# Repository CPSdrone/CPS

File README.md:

# CPS [Custom Printed Submarine]  

Is a project started by Filip Buława, Piotr Domanowski and Marcin Hnat. 
It is about creating a functional product of a innovative submarine, primarily with live streaming from camera in the drone. 
Project is based on 3D printing process, which allows developing various solutions for the form of a drone.

To learn more, find us on
* [Instagram](https://instagram.com/cpsdrone)
* [Facebook](https://facebook.com/cpsdrone)
* [YouTube](https://www.youtube.com/channel/UCqbdxbvG6cqnh_S_RcGnWWg)

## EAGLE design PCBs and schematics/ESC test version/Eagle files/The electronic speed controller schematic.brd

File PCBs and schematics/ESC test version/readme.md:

# ESC test version
This is a work in progress version of our own electronic speed controller for controlling **BLDC** motors featuring **I2C** communication, current and temperature sensors. This is version used only for creating the program and not the final **ESC**!

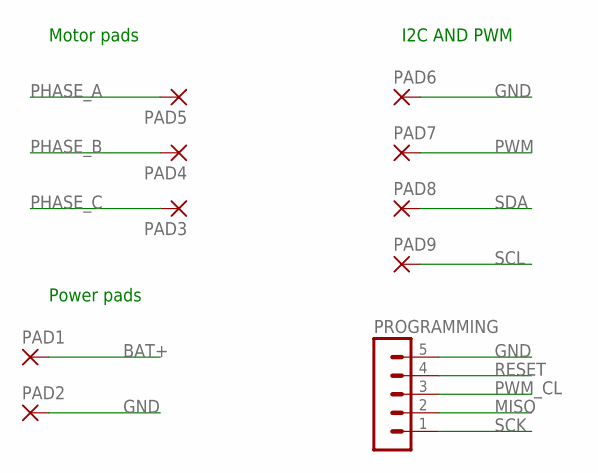
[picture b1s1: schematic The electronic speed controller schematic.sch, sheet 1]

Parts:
PAD1, PAD2, PAD3, PAD4, PAD5: SMD5; SMD2,54-5,08
PAD6, PAD7, PAD8, PAD9: SMD2; SMD1,27-2,54
PROGRAMMING: MA05-1

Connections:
BAT+: PAD1.1; also elsewhere on the board
GND: PAD2.1, PAD6.1, PROGRAMMING.5; also elsewhere on the board
MISO: PROGRAMMING.2; also elsewhere on the board
PHASE_A: PAD5.1; also elsewhere on the board
PHASE_B: PAD4.1; also elsewhere on the board
PHASE_C: PAD3.1; also elsewhere on the board
PWM: PAD7.1; also elsewhere on the board
PWM_CL: PROGRAMMING.3; also elsewhere on the board
RESET: PROGRAMMING.4; also elsewhere on the board
SCK: PROGRAMMING.1; also elsewhere on the board
SCL: PAD9.1; also elsewhere on the board
SDA: PAD8.1; also elsewhere on the board

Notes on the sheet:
Power pads
Motor pads
I2C AND PWM

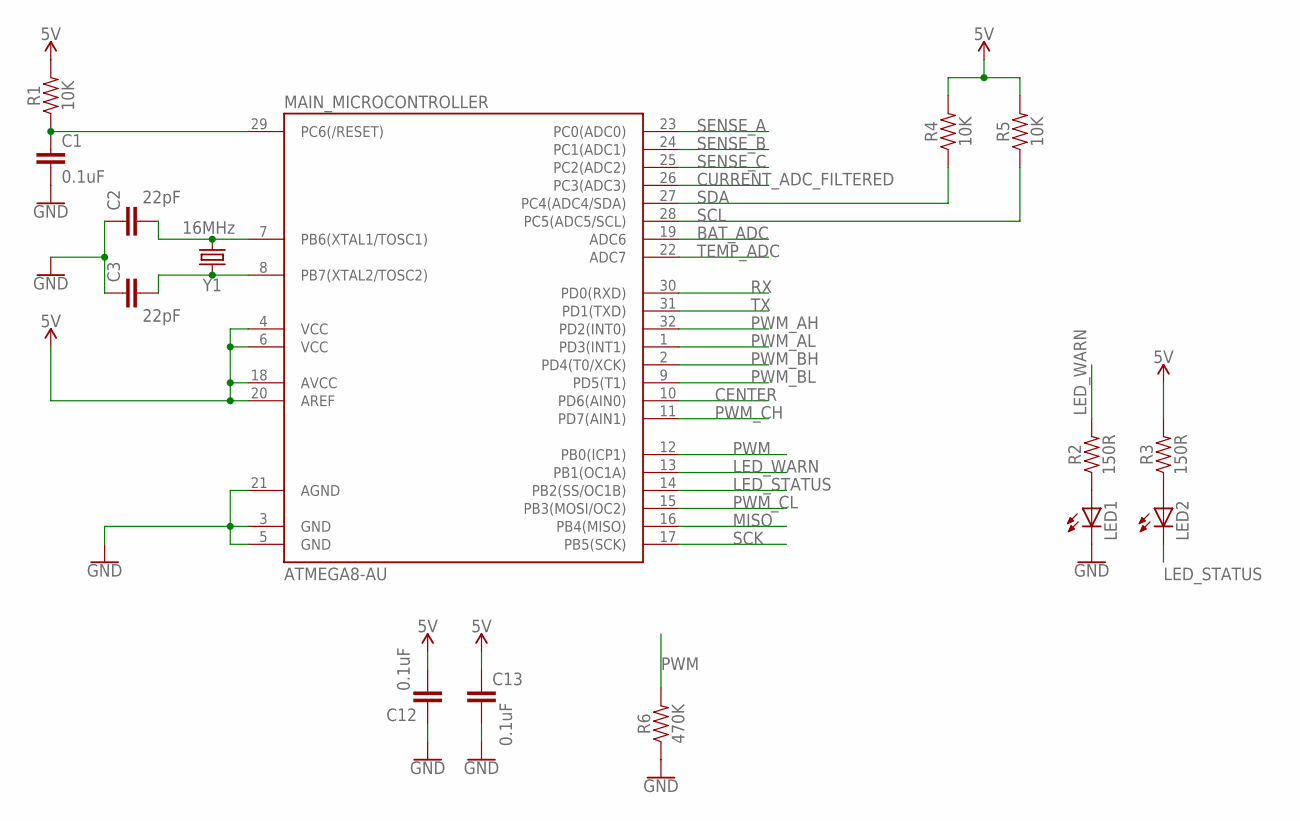
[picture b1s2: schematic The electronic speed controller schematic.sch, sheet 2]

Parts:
C1, C12, C13: 0.1uF; 0805
C2, C3: 22pF; 0805
LED1, LED2: LEDCHIPLED_0805; CHIPLED_0805
MAIN_MICROCONTROLLER: ATMEGA8-AU; TQFP32-08
R1, R4, R5: 10K; 0805
R2, R3: 150R; 0805
R6: 470K; 0805
Y1: 16MHz; CRYSTAL-SMD-5X3.2-4PAD

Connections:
5V: C12.2, C13.1, MAIN_MICROCONTROLLER.4 (VCC), MAIN_MICROCONTROLLER.6 (VCC), MAIN_MICROCONTROLLER.18 (AVCC), MAIN_MICROCONTROLLER.20 (AREF), R1.2, R3.2, R4.2, R5.2; also elsewhere on the board
BAT_ADC: MAIN_MICROCONTROLLER.19 (ADC6); also elsewhere on the board
CENTER: MAIN_MICROCONTROLLER.10 (PD6(AIN0)); also elsewhere on the board
CURRENT_ADC_FILTERED: MAIN_MICROCONTROLLER.26 (PC3(ADC3)); also elsewhere on the board
GND: C1.2, C2.1, C3.1, C12.1, C13.2, LED1.C, MAIN_MICROCONTROLLER.3 (GND), MAIN_MICROCONTROLLER.5 (GND), MAIN_MICROCONTROLLER.21 (AGND), R6.1; also elsewhere on the board
LED_STATUS: LED2.C, MAIN_MICROCONTROLLER.14 (PB2(SS/OC1B))
LED_WARN: MAIN_MICROCONTROLLER.13 (PB1(OC1A)), R2.2
MISO: MAIN_MICROCONTROLLER.16 (PB4(MISO)); also elsewhere on the board
unnamed: C2.2, MAIN_MICROCONTROLLER.7 (PB6(XTAL1/TOSC1)), Y1.3 (2)
unnamed: C3.2, MAIN_MICROCONTROLLER.8 (PB7(XTAL2/TOSC2)), Y1.1
unnamed: LED1.A, R2.1
unnamed: LED2.A, R3.1
PWM: MAIN_MICROCONTROLLER.12 (PB0(ICP1)), R6.2; also elsewhere on the board
PWM_AH: MAIN_MICROCONTROLLER.32 (PD2(INT0)); also elsewhere on the board
PWM_AL: MAIN_MICROCONTROLLER.1 (PD3(INT1)); also elsewhere on the board
PWM_BH: MAIN_MICROCONTROLLER.2 (PD4(T0/XCK)); also elsewhere on the board
PWM_BL: MAIN_MICROCONTROLLER.9 (PD5(T1)); also elsewhere on the board
PWM_CH: MAIN_MICROCONTROLLER.11 (PD7(AIN1)); also elsewhere on the board
PWM_CL: MAIN_MICROCONTROLLER.15 (PB3(MOSI/OC2)); also elsewhere on the board
RESET: C1.1, MAIN_MICROCONTROLLER.29 (PC6(/RESET)), R1.1; also elsewhere on the board
RX: MAIN_MICROCONTROLLER.30 (PD0(RXD))
SCK: MAIN_MICROCONTROLLER.17 (PB5(SCK)); also elsewhere on the board
SCL: MAIN_MICROCONTROLLER.28 (PC5(ADC5/SCL)), R5.1; also elsewhere on the board
SDA: MAIN_MICROCONTROLLER.27 (PC4(ADC4/SDA)), R4.1; also elsewhere on the board
SENSE_A: MAIN_MICROCONTROLLER.23 (PC0(ADC0)); also elsewhere on the board
SENSE_B: MAIN_MICROCONTROLLER.24 (PC1(ADC1)); also elsewhere on the board
SENSE_C: MAIN_MICROCONTROLLER.25 (PC2(ADC2)); also elsewhere on the board
TEMP_ADC: MAIN_MICROCONTROLLER.22 (ADC7); also elsewhere on the board
TX: MAIN_MICROCONTROLLER.31 (PD1(TXD))

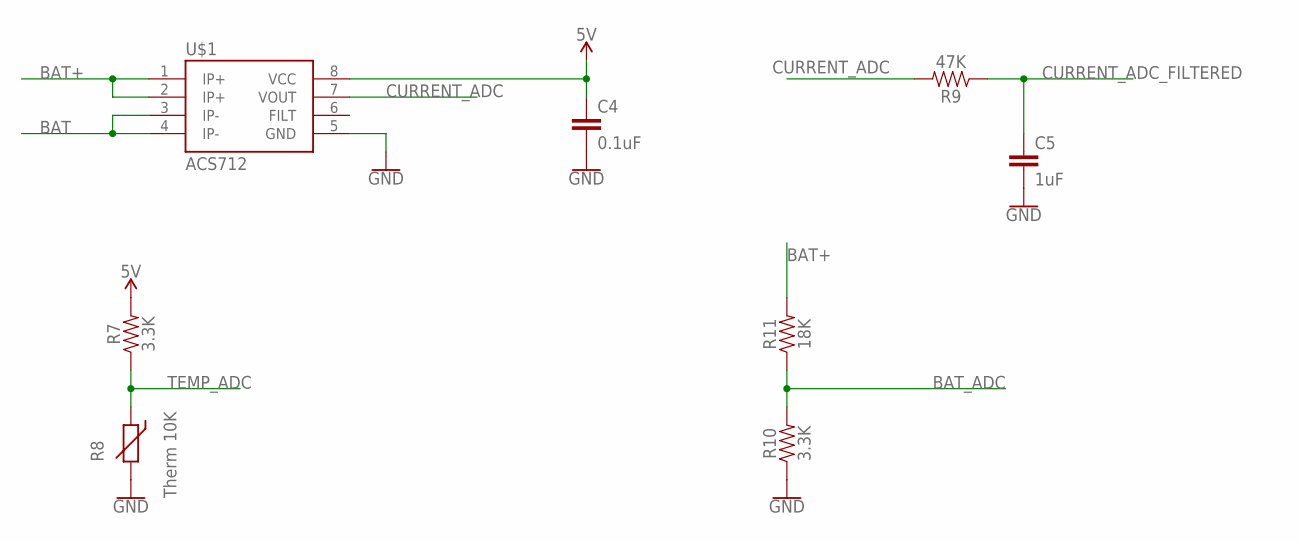
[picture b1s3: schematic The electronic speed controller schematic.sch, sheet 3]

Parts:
C4: 0.1uF; 0805
C5: 1uF; 1206
R7, R10: 3.3K; 0805
R8: Therm 10K; R-5
R9: 47K; 0805
R11: 18K; 0805
U$1: ACS712; SO08

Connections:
5V: C4.1, R7.2, U$1.8 (VCC); also elsewhere on the board
BAT: U$1.3 (IP-), U$1.4 (IP-); also elsewhere on the board
BAT+: R11.2, U$1.1 (IP+), U$1.2 (IP+); also elsewhere on the board
BAT_ADC: R10.2, R11.1; also elsewhere on the board
CURRENT_ADC: R9.2, U$1.7 (VOUT)
CURRENT_ADC_FILTERED: C5.1, R9.1; also elsewhere on the board
GND: C4.2, C5.2, R8.2, R10.1, U$1.5 (GND); also elsewhere on the board
TEMP_ADC: R7.1, R8.1; also elsewhere on the board

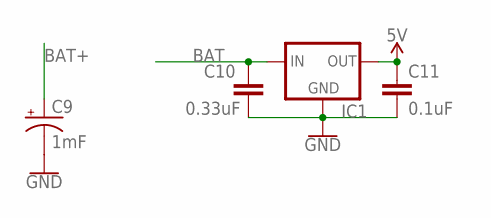
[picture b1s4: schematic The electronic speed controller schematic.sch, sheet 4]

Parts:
C9: 1mF; CPOL-RADIAL-5MM-10MM
C10: 0.33uF; 0805
C11: 0.1uF; 0805
IC1: 78LXX-SOT89; SOT89

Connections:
5V: C11.1, IC1.1 (OUT); also elsewhere on the board
BAT: C10.1, IC1.3 (IN); also elsewhere on the board
BAT+: C9.+; also elsewhere on the board
GND: C9.-, C10.2, C11.2, IC1.2 (GND); also elsewhere on the board

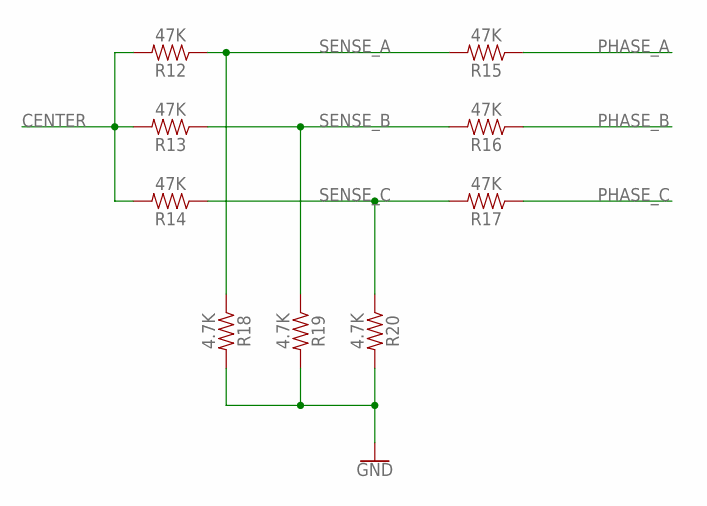
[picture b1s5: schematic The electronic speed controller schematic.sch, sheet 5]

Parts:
R12, R13, R14, R15, R16, R17: 47K; 0805
R18, R19, R20: 4.7K; 0805

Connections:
CENTER: R12.2, R13.2, R14.2; also elsewhere on the board
GND: R18.2, R19.2, R20.2; also elsewhere on the board
PHASE_A: R15.1; also elsewhere on the board
PHASE_B: R16.1; also elsewhere on the board
PHASE_C: R17.1; also elsewhere on the board
SENSE_A: R12.1, R15.2, R18.1; also elsewhere on the board
SENSE_B: R13.1, R16.2, R19.1; also elsewhere on the board
SENSE_C: R14.1, R17.2, R20.1; also elsewhere on the board

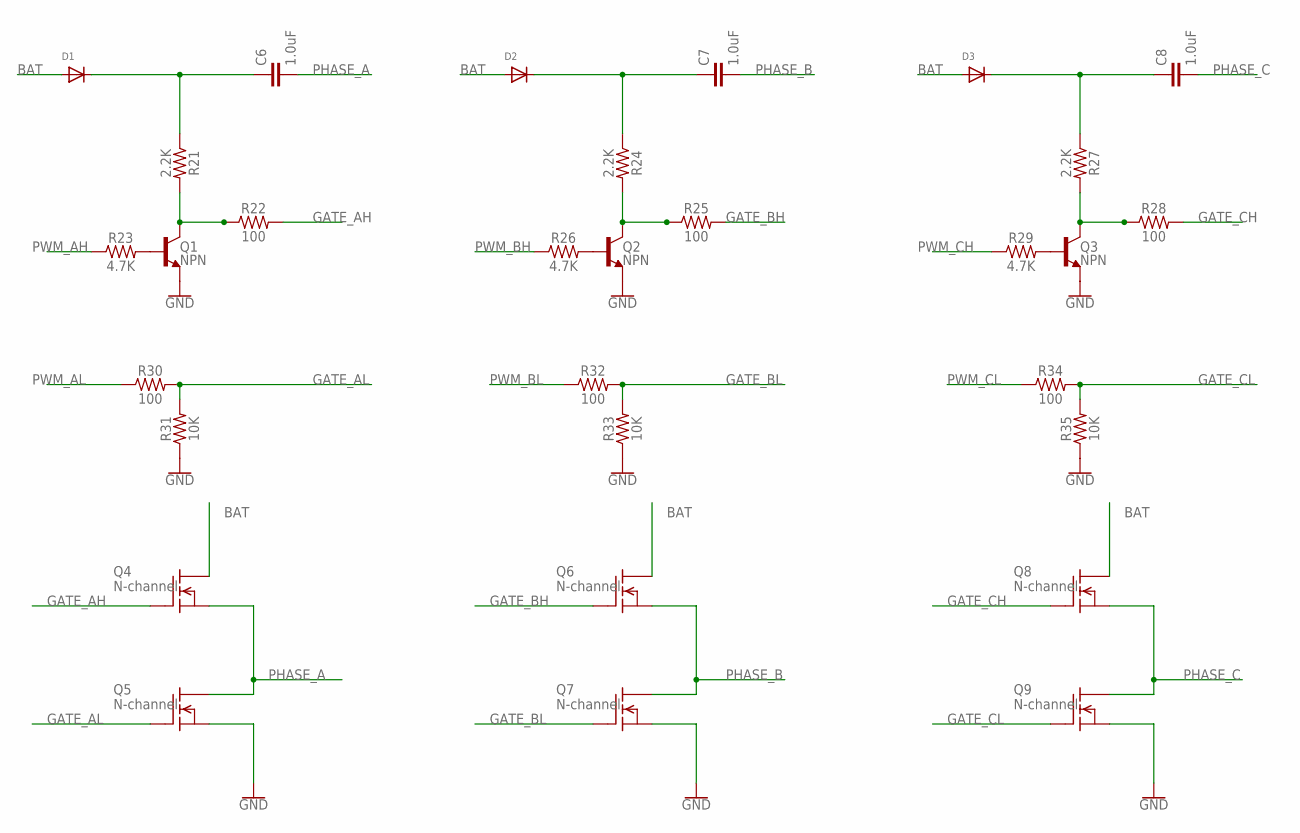
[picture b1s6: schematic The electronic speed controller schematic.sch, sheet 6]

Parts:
C6, C7, C8: 1.0uF; 1206
D1, D2, D3: DIODESOD-123; SOD-123
Q1, Q2, Q3: NPN; SOT23-3
Q4, Q5, Q6, Q7, Q8, Q9: N-channel; TO252
R21, R24, R27: 2.2K; 0805
R22, R25, R28, R30, R32, R34: 100; 0805
R23, R26, R29: 4.7K; 0805
R31, R33, R35: 10K; 0805

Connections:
BAT: D1.A, D2.A, D3.A, Q4.2 (D), Q6.2 (D), Q8.2 (D); also elsewhere on the board
GATE_AH: Q4.1 (G), R22.2
GATE_AL: Q5.1 (G), R30.2, R31.2
GATE_BH: Q6.1 (G), R25.2
GATE_BL: Q7.1 (G), R32.2, R33.2
GATE_CH: Q8.1 (G), R28.2
GATE_CL: Q9.1 (G), R34.2, R35.2
GND: Q1.2 (E), Q2.2 (E), Q3.2 (E), Q5.3 (S), Q7.3 (S), Q9.3 (S), R31.1, R33.1, R35.1; also elsewhere on the board
unnamed: C6.1, D1.C, R21.1
unnamed: Q1.3 (C), R21.2, R22.1
unnamed: Q1.1 (B), R23.2
unnamed: C7.1, D2.C, R24.1
unnamed: Q2.3 (C), R24.2, R25.1
unnamed: Q2.1 (B), R26.2
unnamed: C8.1, D3.C, R27.1
unnamed: Q3.3 (C), R27.2, R28.1
unnamed: Q3.1 (B), R29.2
PHASE_A: C6.2, Q4.3 (S), Q5.2 (D); also elsewhere on the board
PHASE_B: C7.2, Q6.3 (S), Q7.2 (D); also elsewhere on the board
PHASE_C: C8.2, Q8.3 (S), Q9.2 (D); also elsewhere on the board
PWM_AH: R23.1; also elsewhere on the board
PWM_AL: R30.1; also elsewhere on the board
PWM_BH: R26.1; also elsewhere on the board
PWM_BL: R32.1; also elsewhere on the board
PWM_CH: R29.1; also elsewhere on the board
PWM_CL: R34.1; also elsewhere on the board

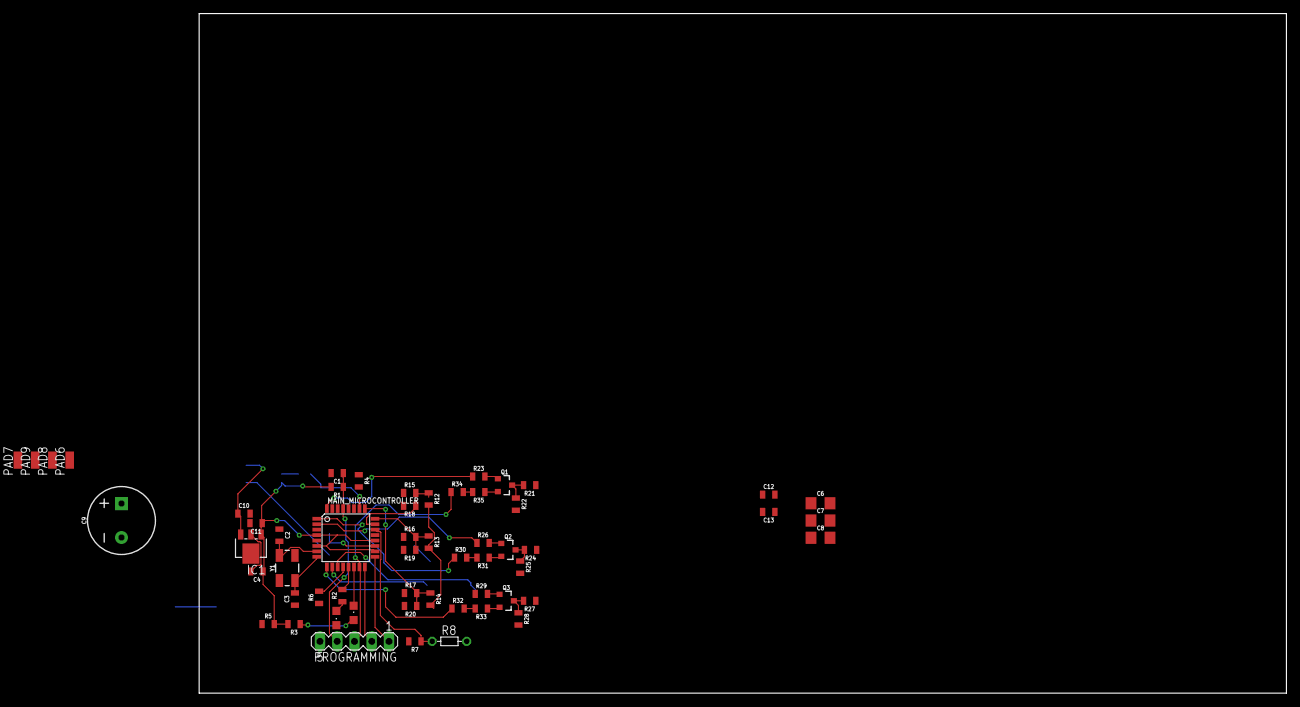
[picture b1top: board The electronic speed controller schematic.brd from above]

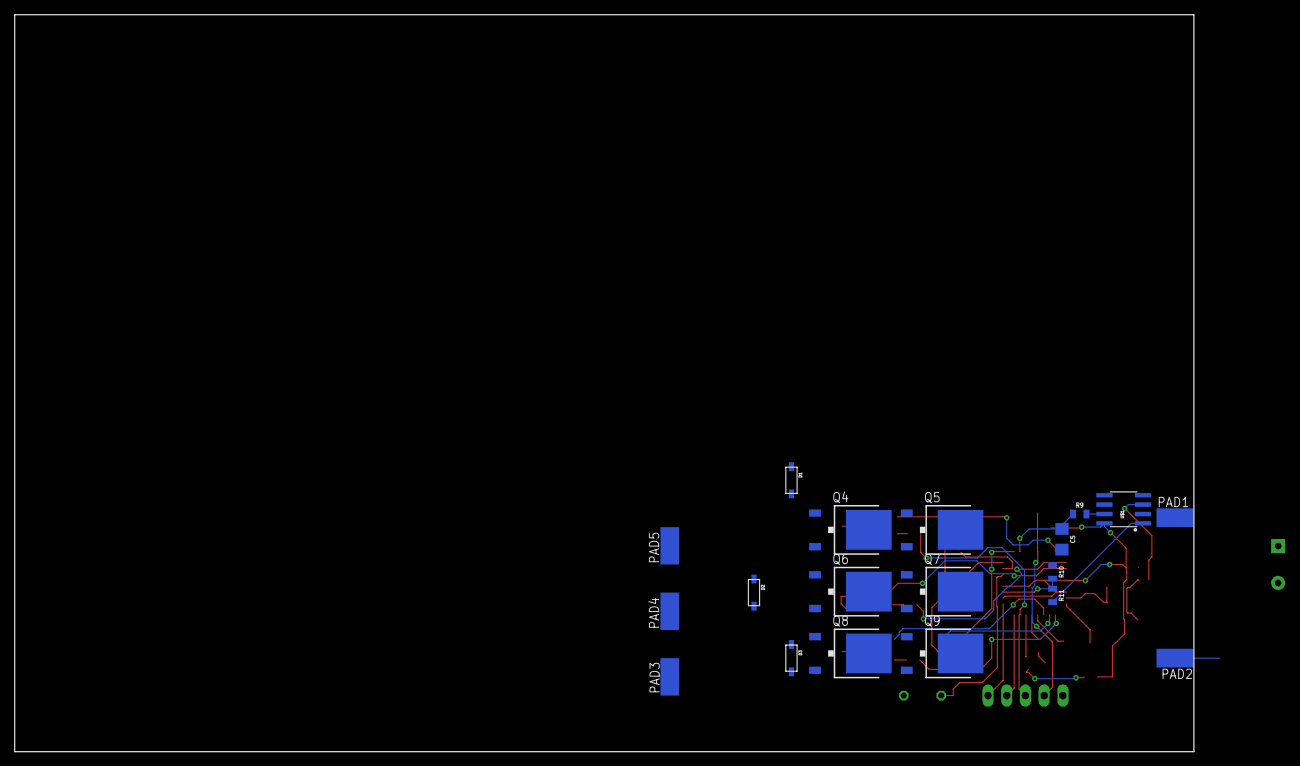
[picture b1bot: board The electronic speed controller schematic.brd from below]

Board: 2 copper layers, 160.0 x 100.0 mm, 76 parts (19 on the bottom side), 48 nets.

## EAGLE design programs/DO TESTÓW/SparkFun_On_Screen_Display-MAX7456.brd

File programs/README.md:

# Welcome to our program storage.
## How to use our programs:

At the moment all of our programs use *Arduino IDE*, so 
1. make sure you installed this program
1. copy all of the libraries to the folder in the directory of your Arduino program, that is `Arduino/libraries`

Generally, the latest programs are the best.
Right now, if you want to use basic CPS code, use version 5.1.
For CPS M, probably `5.0/first_OSD_and_cleanup` is the best.

> Note: **Don't** look at the 1.0 - 2.0 so we won't feel ashamed.

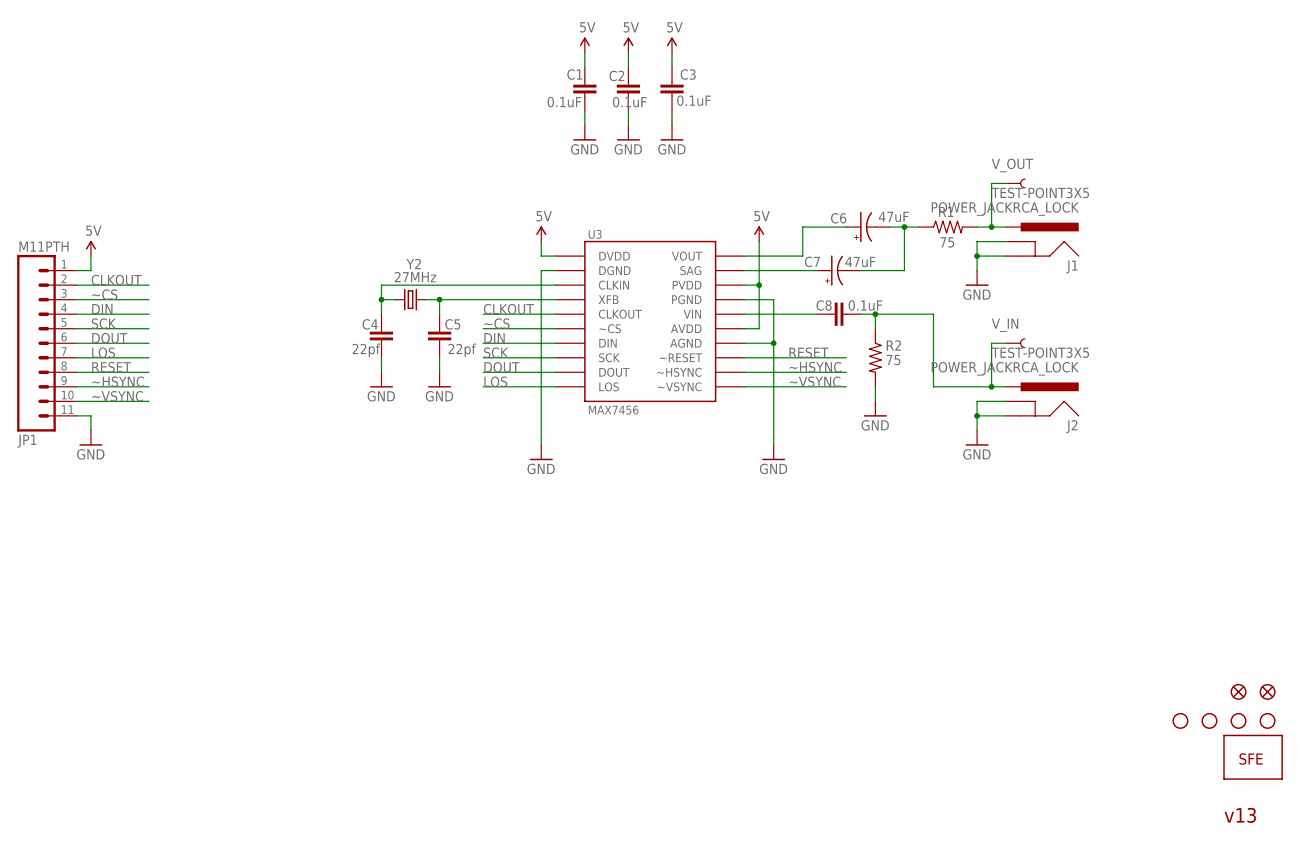
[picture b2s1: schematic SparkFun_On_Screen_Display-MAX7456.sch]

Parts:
C1, C2, C3, C8: 0.1uF; C0402
C4, C5: 22pf; C0402
C6, C7: 47uF; EIA3528
J1, J2: POWER_JACKRCA_LOCK; RCA_LOCK
JP1: M11PTH; 1X11
R1, R2: 75; C0402
U3: MAX7456; TSSOP28
U$2, U$12, U$13, U$14: STAND-OFF
U$8: LOGO-SFENEW; SFE-NEW-WEBLOGO
U$9, U$10: FIDUCIAL1X2; FIDUCIAL-1X2
V_IN: TEST-POINT3X5; PAD.03X.05
V_OUT: TEST-POINT3X5; PAD.03X.05
Y2: 27MHz; CRYSTAL-SMD-5X3

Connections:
5V: C1.2, C2.2, C3.2, JP1.1, U3.3 (DVDD), U3.21 (AVDD), U3.24 (PVDD)
CLKOUT: JP1.2, U3.7 (CLKOUT)
DIN: JP1.4, U3.9 (DIN)
DOUT: JP1.6, U3.11 (DOUT)
GND: C1.1, C2.1, C3.1, C4.1, C5.1, J1.BARREL (GND), J1.SPRING (GNDBREAK), J2.BARREL (GND), J2.SPRING (GNDBREAK), JP1.11, R2.2, U3.4 (DGND), U3.20 (AGND), U3.23 (PGND)
LOS: JP1.7, U3.12 (LOS)
unnamed: C4.2, U3.5 (CLKIN), Y2.3 (2)
unnamed: C5.2, U3.6 (XFB), Y2.1
unnamed: C6.C (-), C7.C (-), R1.1
unnamed: C7.A (+), U3.25 (SAG)
unnamed: C6.A (+), U3.26 (VOUT)
unnamed: J1.BREAK (PWR), R1.2, V_OUT.P$1
unnamed: C8.2, U3.22 (VIN)
unnamed: C8.1, J2.BREAK (PWR), R2.1, V_IN.P$1
RESET: JP1.8, U3.19 (~RESET)
SCK: JP1.5, U3.10 (SCK)
~CS: JP1.3, U3.8 (~CS)
~HSYNC: JP1.9, U3.18 (~HSYNC)
~VSYNC: JP1.10, U3.17 (~VSYNC)

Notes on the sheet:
v13

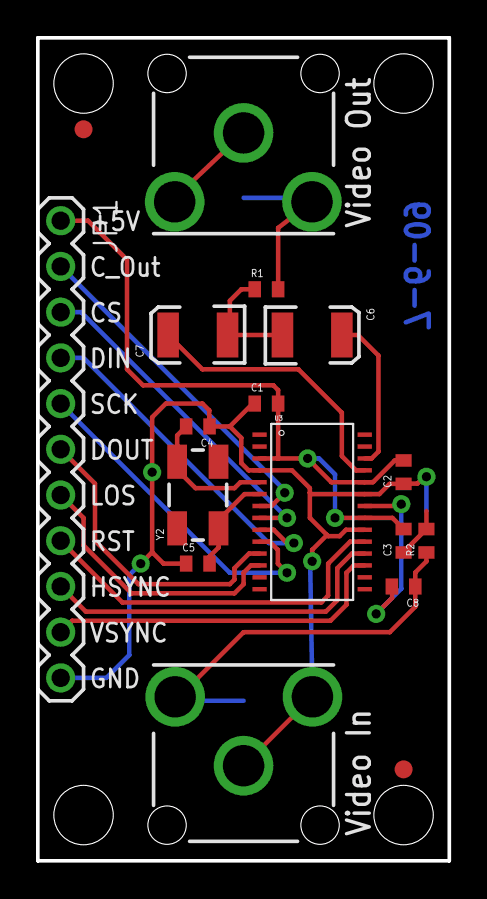
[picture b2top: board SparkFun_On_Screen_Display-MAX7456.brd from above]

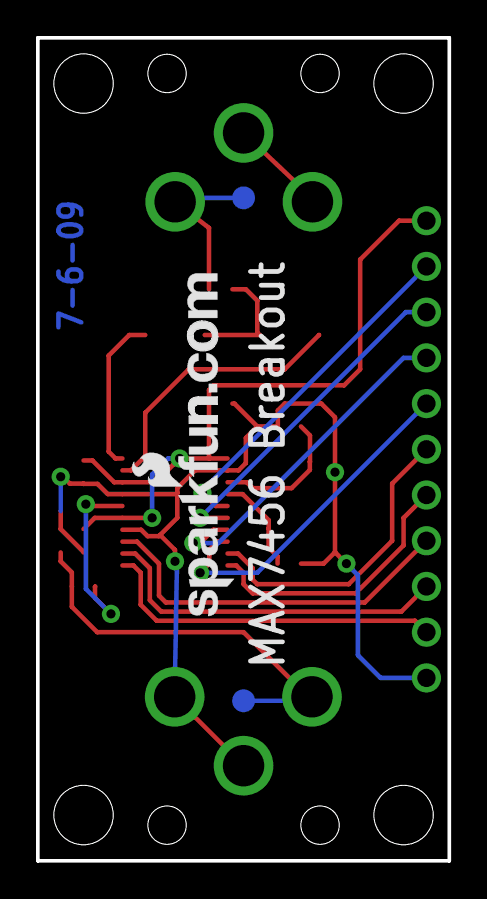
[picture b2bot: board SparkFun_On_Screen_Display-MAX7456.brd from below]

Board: 2 copper layers, 22.9 x 45.7 mm, 24 parts (3 on the bottom side), 19 nets.

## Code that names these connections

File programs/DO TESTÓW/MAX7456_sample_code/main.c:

/*
    MAX7456 test code
	Pete Dokter, 6/17/09
	
	This test code blinks the word "SAMPLE" just under
	where you'd expect someone's face to be.
	
*/

#include <avr/io.h>
#include <avr/interrupt.h>


#define RESET 0	//PB0
#define CS 2	//PB2
#define MOSI 3	//PB3
#define MISO 4	//PB4
#define SCK 5	//PB5


//Define functions
//======================
void ioinit(void);      //Initializes IO
void delay_ms(uint16_t x); //General purpose delay
void delay_us(int x);
void SPI_write(char address, char byte);
char SPI_read(char address);

//======================




int main (void)
{
	char x;

    ioinit(); //Setup IO pins and defaults
	
	delay_ms(1000);
	
	//reset
	PORTB &= ~(1<<RESET);
	delay_ms(1000);
	PORTB |= (1<<RESET);
	delay_ms(1000);
	
	SPI_write(0,0x08);	//enable display of OSD image
	delay_ms(1);
	
	//automatic black level control, have to read, augment and rewrite
	//The data sheet is rather specific about this
	x = SPI_read(0xEC);	
	delay_ms(1);
	x &= 0xEF;
	SPI_write(0x6C,x);
	delay_ms(1);
	
	SPI_write(0x04,0);//DMM set to 0
	
	x = 25;
	
	SPI_write(0x05,0x01);//DMAH
	
	SPI_write(0x06,x);//DMAL
	SPI_write(0x07,0x1D);
	
	SPI_write(0x06,x+1);//DMAL
	SPI_write(0x07,0x0B);
	
	SPI_write(0x06,x+2);//DMAL
	SPI_write(0x07,0x17);
	
	SPI_write(0x06,x+3);//DMAL
	SPI_write(0x07,0x1A);
	
	SPI_write(0x06,x+4);//DMAL
	SPI_write(0x07,0x16);
	
	SPI_write(0x06,x+6);//DMAL
	SPI_write(0x07,0x0F);
	
	
	while(1)
	{
		SPI_write(0,0x08);	//enable display of OSD image
		delay_ms(1000);
		SPI_write(0,0);	//disable display of OSD image
		delay_ms(1000);
	}
	
	
}

void ioinit (void)
{
	PORTB = 0xFF;
	DDRB = ((1<<CS) | (1<<MOSI) | (1<<SCK) | (1<<RESET));

    TCCR2B = (1<<CS21); //Set Prescaler to 8. CS21=1

}

//General short delays
void delay_us(int x)
{
	int y, z, a;
	
	y = x/256;
	z = x - y * 256;
	
	for (a = 0; a < y; a++)
	{
		TIFR2 |= 0x01;//Clear any interrupt flags on Timer2
		
		TCNT2 = 0; //256 - 125 = 131 : Preload timer 2 for x clicks. Should be 1us per click
	
		while(!(TIFR2 & 0x01));
		
	}
	
	TIFR2 |= 0x01;//Clear any interrupt flags on Timer2
	
	TCNT2 = 256-z; //256 - 125 = 131 : Preload timer 2 for x clicks. Should be 1us per click

	while(!(TIFR2 & 0x01));
	
}

//General short delays
void delay_ms(uint16_t x)
{
	for (; x > 0 ; x--)
    {
        delay_us(250);
        delay_us(250);
        delay_us(250);
        delay_us(250);
    }
	
}

void SPI_write(char address, char byte)
{
	unsigned char SPICount;                                       // Counter used to clock out the data

	unsigned char SPIData;                                        // Define a data structure for the SPI data
	
	PORTB |= (1<<CS);                                        		// Make sure we start with active-low CS high
	PORTB &= ~(1<<SCK);                                       		// and CK low
	
	SPIData = address;                                            // Preload the data to be sent with Address
	PORTB &= ~(1<<CS);                                           // Set active-low CS low to start the SPI cycle 

	
	for (SPICount = 0; SPICount < 8; SPICount++)                  // Prepare to clock out the Address byte
	{
		if (SPIData & 0x80) PORTB |= (1<<MOSI);           				// Check for a 1 and set the MOSI line appropriately

		else PORTB &= ~(1<<MOSI);
		
		PORTB |= (1<<SCK);                                         // Toggle the clock line
		PORTB &= ~(1<<SCK);
		
		SPIData <<= 1;                                              // Rotate to get the next bit
	}                                                             // and loop back to send the next bit
														
																// Repeat for the Data byte
	SPIData = byte;                                            // Preload the data to be sent with Data
	
	for (SPICount = 0; SPICount < 8; SPICount++)
	{
		if (SPIData & 0x80) PORTB |= (1<<MOSI);

		else PORTB &= ~(1<<MOSI);
		
		PORTB |= (1<<SCK); 
		PORTB &= ~(1<<SCK);
		
		SPIData <<= 1; 
	}           
	
	PORTB |= (1<<CS);
	PORTB &= ~(1<<MOSI);

}


char SPI_read(char address)
{
	unsigned char SPICount;                                       // Counter used to clock out the data
  
	char SPIData; 
	char temp;
	
	PORTB |= (1<<CS);                                        		// Make sure we start with active-low CS high
	PORTB &= ~(1<<SCK);                                       		// and CK low
	
	SPIData = address;                                            // Preload the data to be sent with Address
	PORTB &= ~(1<<CS);                                           // Set active-low CS low to start the SPI cycle 

	
	for (SPICount = 0; SPICount < 8; SPICount++)                  // Prepare to clock out the Address byte
	{
		if (SPIData & 0x80) PORTB |= (1<<MOSI);           				// Check for a 1 and set the MOSI line appropriately

		else PORTB &= ~(1<<MOSI);
		
		PORTB |= (1<<SCK);                                         // Toggle the clock line
		PORTB &= ~(1<<SCK);
		
		SPIData <<= 1;                                              // Rotate to get the next bit
	}                                                             // and loop back to send the next bit
	

	PORTB &= ~(1<<MOSI);                                         // Reset the MOSI data line
	
	SPIData = 0;
	
	for (SPICount = 0; SPICount < 8; SPICount++)                  // Prepare to clock in the data to be read
	{
		SPIData <<=1;                                               // Rotate the data
		PORTB |= (1<<SCK);                                         // Raise the clock to clock the data out of the MAX7456
		
		temp = PINB;
		if (temp & (1<<MISO)) SPIData |= 1;                       // Read the data bit
		
		PORTB &= ~(1<<SCK);                                       // Drop the clock ready for the next bit
	}                                                             // and loop back
	PORTB |= (1<<CS);                                                 // Raise CS
					  
	return SPIData;                              // Finally return the read data


}

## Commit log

2020-01-14 szympans
2020-01-14 go fuck yourself
2020-01-14 banan z szynka
2020-01-14 on a tree
2020-01-14 helena
2020-01-14 trouble
2020-01-14 bumba
2020-01-14 added manipulator stls
2020-01-14 f3d file
2020-01-14 mount
2020-01-14 help
2020-01-14 deleted crap
2020-01-15 Programs
2020-01-15 base program
2020-01-15 added sorting filders
2020-01-15 shortcut
2020-01-15 libraries
2020-01-15 programs organization
2020-01-15 read me of codes
2020-01-15 readme organisation
2020-01-15 CPS yes
2020-01-16 updated base program
2020-02-13 glass model is better
2020-02-13 % add
2020-02-23 modules,lights,pH
2020-02-29 major steps in the program teritory
2020-03-03 cool
2020-03-05 yup, thats it
2020-03-05 made changes
2020-04-08 IMU&PID
2020-04-27 a lot
2020-04-29 here you go
2020-05-09 toto
2020-05-16 code for the world
2020-05-22 added ESC files in the PCB folder
2020-05-22 collection
2020-05-22 changed a folder name cuz FILIP didn't like it
2020-05-28 Auto stash before merge of "master" and "origin/master"
2020-05-28 created a readme
2020-05-28 Fixed some links
2020-05-28 Fixed up my mess
    Deleted unnecessary and potentially personal files
2020-05-28 fixed stuff for poitrek
2020-06-24 mrówka
2020-06-24 just sth
2022-08-04 updated status

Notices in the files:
parts and their libraries:
SparkFun-Capacitors: Licensing: Creative Commons ShareAlike 4.0 International - https://creativecommons.org/licenses/by-sa/4.0
